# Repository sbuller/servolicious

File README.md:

A 16 port servo controller. Supply +5V, SDA and SCL.

Servo control is generally pulse widths of 1000-2000us, produced at 50Hz where
one wavelength is 20ms. The PCA9685 does 12bit PWM, counting to 4096. Each
count corresponds to 4.883 us. 1000us is a count of 204.7. A count of 204 should
thus drive a servo fully to one side. 2000us is then 409.4. A count of 410 should
thus drive a servo fully to the other side.

Let x be the position to drive the servo to, between 0 and 1.

y = round( x * (410-204) + 204 )

Now y is the count for which each pulse should be held high.

Phase isn't likely to be important. Set LEDn_ON to 0. Set LEDn_OFF to y.

If necessary, the resolution of the PWM can be improved. By scaling the clock
and adjusting the PWM for each segment, finer control may be managed.

```
Segments: 10
Clock: 500Hz
Segment 1: 2048-4096
Segment 2-10: off
```

```
Segments: 4
Clock: 200Hz
Segment 1: 819-1639
Segments 2-4: off
```

```
Segments: 5
Clock: 250Hz
Segment 1: 1024-2048
Segments 2-5: off
```

```
Segments: 20
Clock: 1000Hz
Segment 1: on
Segment 2: 0-4096
Segments 3-20: off
```

If not controlling /OE and CLK from the uC, pull low. R1 and R2 are
provided for this purpose.

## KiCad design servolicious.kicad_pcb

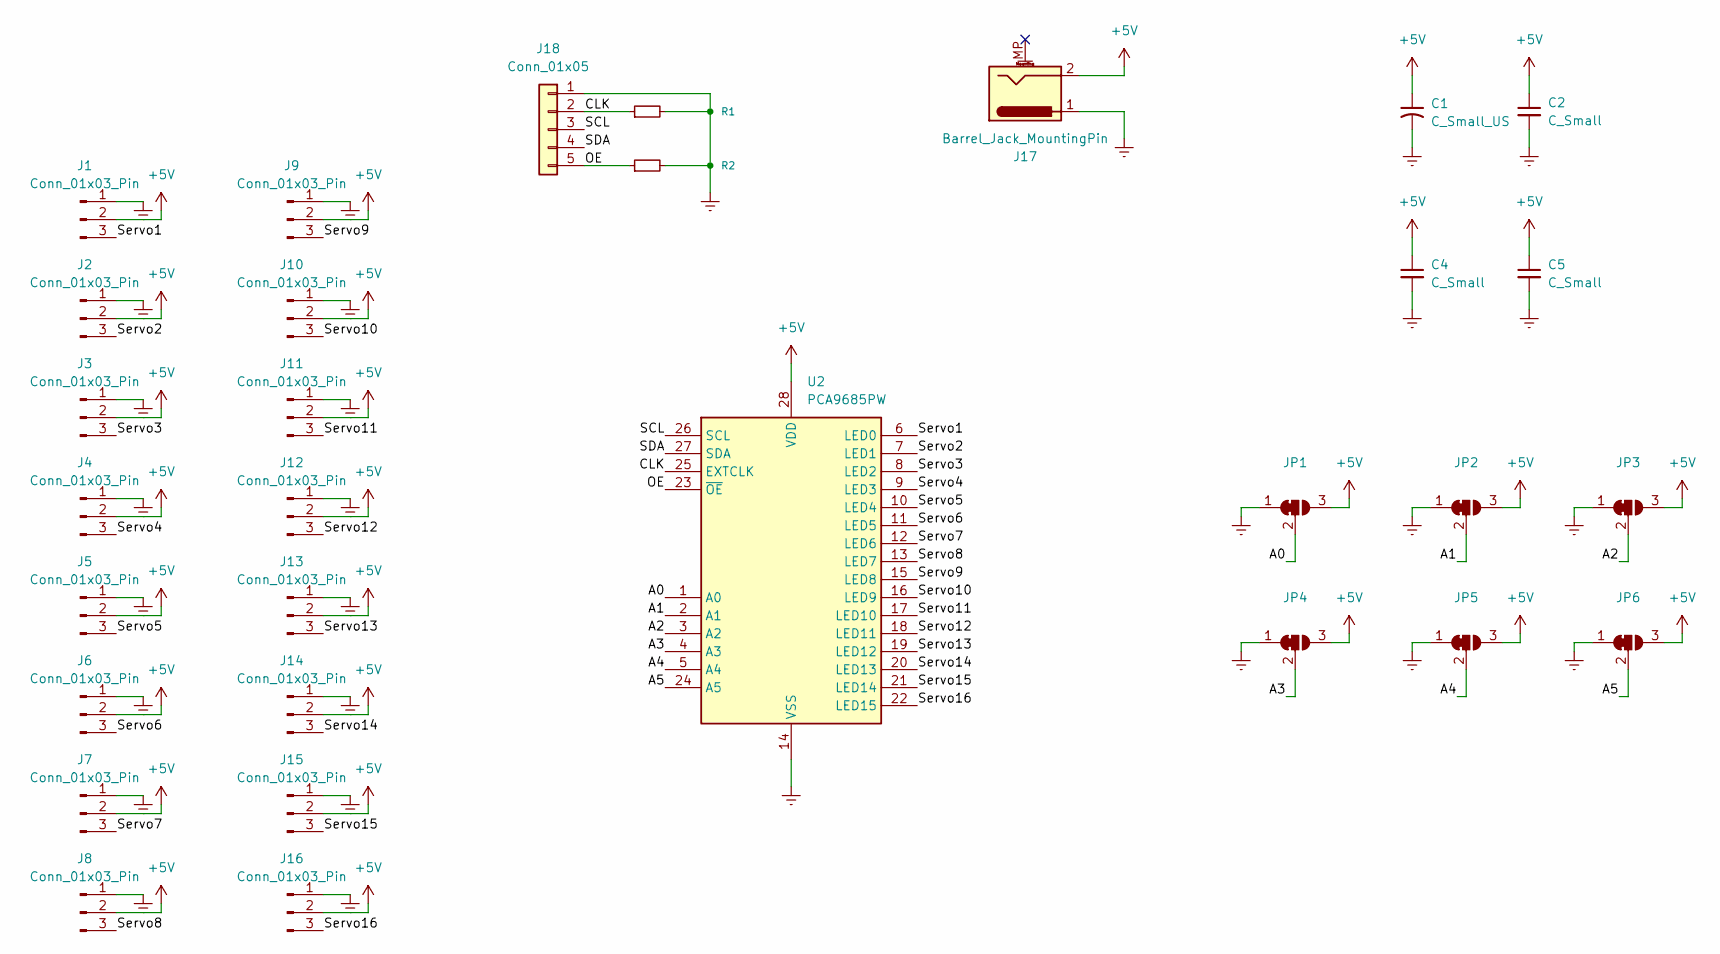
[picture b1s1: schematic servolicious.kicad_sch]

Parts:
C1: C_Small_US; C_Radial_D8.0mm_H11.5mm_P3.50mm
C2: C_Small; C_0603_1608Metric_Pad1.08x0.95mm_HandSolder
C4, C5: C_Small; C_1206_3216Metric_Pad1.33x1.80mm_HandSolder
J1, J2, J3, J4, J5, J6, J7, J8, J9, J10, J11, J12, J13, J14, J15, J16: Conn_01x03_Pin; PinHeader_1x03_P2.54mm_Vertical
J17: Barrel_Jack_MountingPin; BarrelJack_Horizontal
J18: Conn_01x05; PinHeader_1x05_P2.54mm_Vertical
JP1, JP2, JP3, JP4, JP5, JP6: Jumper:SolderJumper-3_P1.3mm_Bridged12_RoundedPad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; SolderJumper-3_P1.3mm_Bridged12_RoundedPad1.0x1.5mm
R1, R2: R_Small; R_0603_1608Metric_Pad0.98x0.95mm_HandSolder
U2: PCA9685PW; TSSOP-28_4.4x9.7mm_P0.65mm

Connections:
+5V: C1.1, C2.1, C4.1, C5.1, J1.2, J2.2, J3.2, J4.2, J5.2, J6.2, J7.2, J8.2, J9.2, J10.2, J11.2, J12.2, J13.2, J14.2, J15.2, J16.2, J17.2, JP1.3 (B), JP2.3 (B), JP3.3 (B), JP4.3 (B), JP5.3 (B), JP6.3 (B), U2.28 (VDD)
/A0: JP1.2 (C), U2.1 (A0)
/A1: JP2.2 (C), U2.2 (A1)
/A2: JP3.2 (C), U2.3 (A2)
/A3: JP4.2 (C), U2.4 (A3)
/A4: JP5.2 (C), U2.5 (A4)
/A5: JP6.2 (C), U2.24 (A5)
/CLK: J18.2, R1.1, U2.25 (EXTCLK)
/OE: J18.5, R2.1, U2.23 (~OE)
/SCL: J18.3, U2.26 (SCL)
/SDA: J18.4, U2.27 (SDA)
/Servo1: J1.3, U2.6 (LED0)
/Servo2: J2.3, U2.7 (LED1)
/Servo3: J3.3, U2.8 (LED2)
/Servo4: J4.3, U2.9 (LED3)
/Servo5: J5.3, U2.10 (LED4)
/Servo6: J6.3, U2.11 (LED5)
/Servo7: J7.3, U2.12 (LED6)
/Servo8: J8.3, U2.13 (LED7)
/Servo9: J9.3, U2.15 (LED8)
/Servo10: J10.3, U2.16 (LED9)
/Servo11: J11.3, U2.17 (LED10)
/Servo12: J12.3, U2.18 (LED11)
/Servo13: J13.3, U2.19 (LED12)
/Servo14: J14.3, U2.20 (LED13)
/Servo15: J15.3, U2.21 (LED14)
/Servo16: J16.3, U2.22 (LED15)
Earth: C1.2, C2.2, C4.2, C5.2, J1.1, J2.1, J3.1, J4.1, J5.1, J6.1, J7.1, J8.1, J9.1, J10.1, J11.1, J12.1, J13.1, J14.1, J15.1, J16.1, J17.1, J18.1, JP1.1 (A), JP2.1 (A), JP3.1 (A), JP4.1 (A), JP5.1 (A), JP6.1 (A), R1.2, R2.2, U2.14 (VSS)

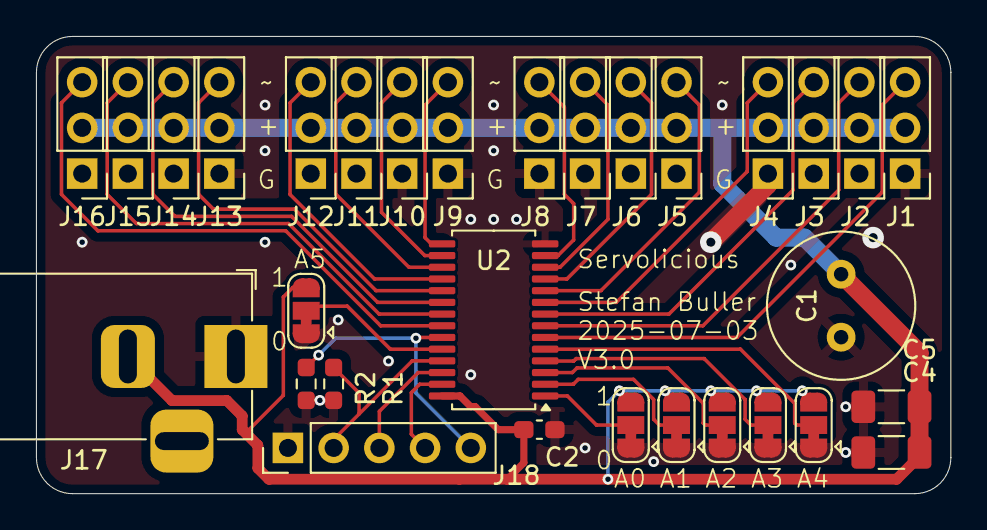
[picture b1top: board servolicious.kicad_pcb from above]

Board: 2 copper layers, 50.8 x 25.4 mm, 31 parts (0 on the bottom side), 28 nets.

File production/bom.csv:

Designator,Footprint,Quantity,Value,LCSC Part #
C1,C_Radial_D8.0mm_H11.5mm_P3.50mm,1,C_Small_US,
C2,0603,1,C_Small,
"C4, C5",1206,2,C_Small,
"J1, J10, J11, J12, J13, J14, J15, J16, J2, J3, J4, J5, J6, J7, J8, J9",PinHeader_1x03_P2.54mm_Vertical,16,Conn_01x03_Pin,
J17,BarrelJack_Horizontal,1,Barrel_Jack_MountingPin,
J18,PinHeader_1x05_P2.54mm_Vertical,1,Conn_01x05,
"R1, R2",0603,2,R_Small,
U2,TSSOP-28_4.4x9.7mm_P0.65mm,1,PCA9685PW,

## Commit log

2025-07-02 Servolicious
2025-07-02 Servo headers were wrong
2025-07-02 Add pretty
2025-07-02 Switch to latched shift register
2025-07-02 Add daisy out
2025-07-02 Add data on servo control to readme
2025-07-03 Use the PCA9685
2025-07-03 Update README for PCA9685 and rotate cap to allow it to be bent over
2025-07-03 Interactive PWM control for finer grained management of servos
